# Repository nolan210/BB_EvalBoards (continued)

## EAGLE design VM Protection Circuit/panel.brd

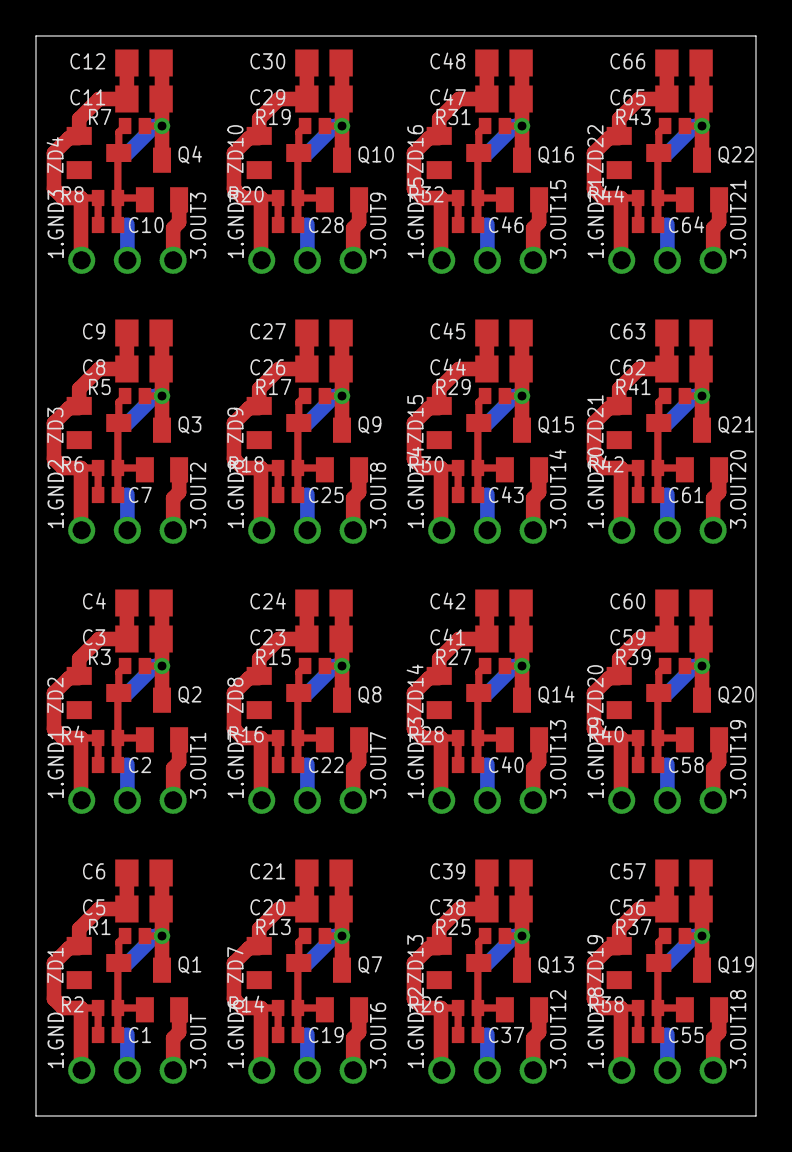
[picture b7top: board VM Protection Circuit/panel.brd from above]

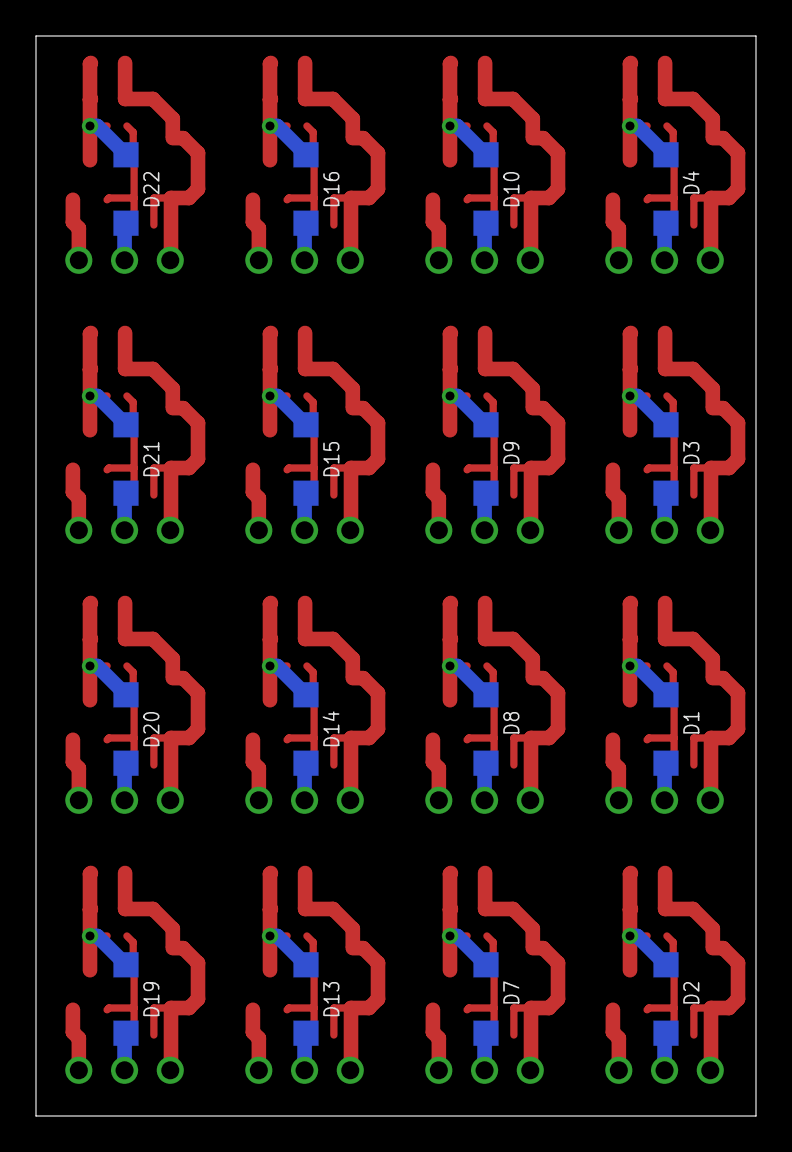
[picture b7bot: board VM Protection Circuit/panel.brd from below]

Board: 2 copper layers, 40.0 x 60.0 mm, 176 parts (16 on the bottom side), 80 nets.

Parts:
1.GND, 1.GND1, 1.GND2, 1.GND3, 1.GND6, 1.GND7, 1.GND8, 1.GND9, 1.GND12, 1.GND13, 1.GND14, 1.GND15, 1.GND18, 1.GND19, 1.GND20, 1.GND21, 2.PWR, 2.PWR1, 2.PWR2, 2.PWR3, 2.PWR6, 2.PWR7, 2.PWR8, 2.PWR9, 2.PWR12, 2.PWR13, 2.PWR14, 2.PWR15, 2.PWR18, 2.PWR19, 2.PWR20, 2.PWR21, 3.OUT, 3.OUT1, 3.OUT2, 3.OUT3, 3.OUT6, 3.OUT7, 3.OUT8, 3.OUT9, 3.OUT12, 3.OUT13, 3.OUT14, 3.OUT15, 3.OUT18, 3.OUT19, 3.OUT20, 3.OUT21: TESTPOINTKE5000-SMTEXT; PINS_1_TESTPOINT_KE5000_NOTEXT
C1, C2, C7, C10, C19, C22, C25, C28, C37, C40, C43, C46, C55, C58, C61, C64: 1u; C0402
C3, C4, C5, C6, C8, C9, C11, C12, C20, C21, C23, C24, C26, C27, C29, C30, C38, C39, C41, C42, C44, C45, C47, C48, C56, C57, C59, C60, C62, C63, C65, C66: 4u7 50V; C0805
D1, D2, D3, D4, D7, D8, D9, D10, D13, D14, D15, D16, D19, D20, D21, D22: SM4001PL; SOD123
Q1, Q2, Q3, Q4, Q7, Q8, Q9, Q10, Q13, Q14, Q15, Q16, Q19, Q20, Q21, Q22: RYC002N05T316; SOT23
R1, R3, R5, R7, R13, R15, R17, R19, R25, R27, R29, R31, R37, R39, R41, R43: 10k; R0402
R2, R4, R6, R8, R14, R16, R18, R20, R26, R28, R30, R32, R38, R40, R42, R44: 499k; R0402
ZD1, ZD2, ZD3, ZD4, ZD7, ZD8, ZD9, ZD10, ZD13, ZD14, ZD15, ZD16, ZD19, ZD20, ZD21, ZD22: 15V; SOT23

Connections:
B+: 2.PWR.1, D2.A
B+1: 2.PWR1.1, D1.A
B+2: 2.PWR2.1, D3.A
B+3: 2.PWR3.1, D4.A
B+6: 2.PWR6.1, D7.A
B+7: 2.PWR7.1, D8.A
B+8: 2.PWR8.1, D9.A
B+9: 2.PWR9.1, D10.A
B+12: 2.PWR12.1, D13.A
B+13: 2.PWR13.1, D14.A
B+14: 2.PWR14.1, D15.A
B+15: 2.PWR15.1, D16.A
B+18: 2.PWR18.1, D19.A
B+19: 2.PWR19.1, D20.A
B+20: 2.PWR20.1, D21.A
B+21: 2.PWR21.1, D22.A
GND: 1.GND.1, C1.2, C5.2, C6.2, R2.1, ZD1.1
GND1: 1.GND1.1, C2.2, C3.2, C4.2, R4.1, ZD2.1
GND2: 1.GND2.1, C7.2, C8.2, C9.2, R6.1, ZD3.1
GND3: 1.GND3.1, C10.2, C11.2, C12.2, R8.1, ZD4.1
GND6: 1.GND6.1, C19.2, C20.2, C21.2, R14.1, ZD7.1
GND7: 1.GND7.1, C22.2, C23.2, C24.2, R16.1, ZD8.1
GND8: 1.GND8.1, C25.2, C26.2, C27.2, R18.1, ZD9.1
GND9: 1.GND9.1, C28.2, C29.2, C30.2, R20.1, ZD10.1
GND12: 1.GND12.1, C37.2, C38.2, C39.2, R26.1, ZD13.1
GND13: 1.GND13.1, C40.2, C41.2, C42.2, R28.1, ZD14.1
GND14: 1.GND14.1, C43.2, C44.2, C45.2, R30.1, ZD15.1
GND15: 1.GND15.1, C46.2, C47.2, C48.2, R32.1, ZD16.1
GND18: 1.GND18.1, C55.2, C56.2, C57.2, R38.1, ZD19.1
GND19: 1.GND19.1, C58.2, C59.2, C60.2, R40.1, ZD20.1
GND20: 1.GND20.1, C61.2, C62.2, C63.2, R42.1, ZD21.1
GND21: 1.GND21.1, C64.2, C65.2, C66.2, R44.1, ZD22.1
Q1.DRAIN: C5.1, C6.1, D2.C, Q1.3, R1.2
Q1.DRAIN1: C3.1, C4.1, D1.C, Q2.3, R3.2
Q1.DRAIN2: C8.1, C9.1, D3.C, Q3.3, R5.2
Q1.DRAIN3: C11.1, C12.1, D4.C, Q4.3, R7.2
Q1.DRAIN6: C20.1, C21.1, D7.C, Q7.3, R13.2
Q1.DRAIN7: C23.1, C24.1, D8.C, Q8.3, R15.2
Q1.DRAIN8: C26.1, C27.1, D9.C, Q9.3, R17.2
Q1.DRAIN9: C29.1, C30.1, D10.C, Q10.3, R19.2
Q1.DRAIN12: C38.1, C39.1, D13.C, Q13.3, R25.2
Q1.DRAIN13: C41.1, C42.1, D14.C, Q14.3, R27.2
Q1.DRAIN14: C44.1, C45.1, D15.C, Q15.3, R29.2
Q1.DRAIN15: C47.1, C48.1, D16.C, Q16.3, R31.2
Q1.DRAIN18: C56.1, C57.1, D19.C, Q19.3, R37.2
Q1.DRAIN19: C59.1, C60.1, D20.C, Q20.3, R39.2
Q1.DRAIN20: C62.1, C63.1, D21.C, Q21.3, R41.2
Q1.DRAIN21: C65.1, C66.1, D22.C, Q22.3, R43.2
Q1.GATE: C1.1, Q1.1, R1.1, R2.2, ZD1.3
Q1.GATE1: C2.1, Q2.1, R3.1, R4.2, ZD2.3
Q1.GATE2: C7.1, Q3.1, R5.1, R6.2, ZD3.3
Q1.GATE3: C10.1, Q4.1, R7.1, R8.2, ZD4.3
Q1.GATE6: C19.1, Q7.1, R13.1, R14.2, ZD7.3
Q1.GATE7: C22.1, Q8.1, R15.1, R16.2, ZD8.3
Q1.GATE8: C25.1, Q9.1, R17.1, R18.2, ZD9.3
Q1.GATE9: C28.1, Q10.1, R19.1, R20.2, ZD10.3
Q1.GATE12: C37.1, Q13.1, R25.1, R26.2, ZD13.3
Q1.GATE13: C40.1, Q14.1, R27.1, R28.2, ZD14.3
Q1.GATE14: C43.1, Q15.1, R29.1, R30.2, ZD15.3
Q1.GATE15: C46.1, Q16.1, R31.1, R32.2, ZD16.3
Q1.GATE18: C55.1, Q19.1, R37.1, R38.2, ZD19.3
Q1.GATE19: C58.1, Q20.1, R39.1, R40.2, ZD20.3
Q1.GATE20: C61.1, Q21.1, R41.1, R42.2, ZD21.3
Q1.GATE21: C64.1, Q22.1, R43.1, R44.2, ZD22.3
VM: 3.OUT.1, Q1.2
VM1: 3.OUT1.1, Q2.2
VM2: 3.OUT2.1, Q3.2
VM3: 3.OUT3.1, Q4.2
VM6: 3.OUT6.1, Q7.2
VM7: 3.OUT7.1, Q8.2
VM8: 3.OUT8.1, Q9.2
VM9: 3.OUT9.1, Q10.2
VM12: 3.OUT12.1, Q13.2
VM13: 3.OUT13.1, Q14.2
VM14: 3.OUT14.1, Q15.2
VM15: 3.OUT15.1, Q16.2
VM18: 3.OUT18.1, Q19.2
VM19: 3.OUT19.1, Q20.2
VM20: 3.OUT20.1, Q21.2
VM21: 3.OUT21.1, Q22.2

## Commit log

2021-03-03 02MAR2021
2021-03-03 20210303
2021-03-05 20210304
2021-03-09 20210309
2021-03-11 20210310
2021-03-13 20210313
2021-03-15 20210314
2021-03-16 20210315
